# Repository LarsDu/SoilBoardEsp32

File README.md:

# SoilBoardEsp32

A custom PCB for the ESP32-S3-WROOM-1 designed for WiFi enabled and battery powered automated plant watering.

Could also be used to control a dual propeller drone.

Certain parts of the circuit schematic were sourced/adapted from the [LiteWing](https://github.com/Circuit-Digest/LiteWing/tree/main) open source drone project.

Setup with:
 - 2 Screw terminals for 3-4V DC water pumps
 - 2 Capacitative soil moisture sensors
 - Either a DHT-40 or AHT-40 temperature/humidity sensor
 - An optional TFT display
 - 2 optional servo headers
 - An optional ping sensor header for water level detection

This is my first-time PCB design and assembly attempt. This repo may be updated as I make more progress on actual construction.

# Getting started

Board schematics can be opened in KiCad under [`hardware/soilboard/soilboard.kicad_pro`](hardware/soilboard/soilboard.kicad_pro).

Gerber files for each production version can be found under [`hardware/soilboard/production/`](hardware/soilboard/production/)

## Images

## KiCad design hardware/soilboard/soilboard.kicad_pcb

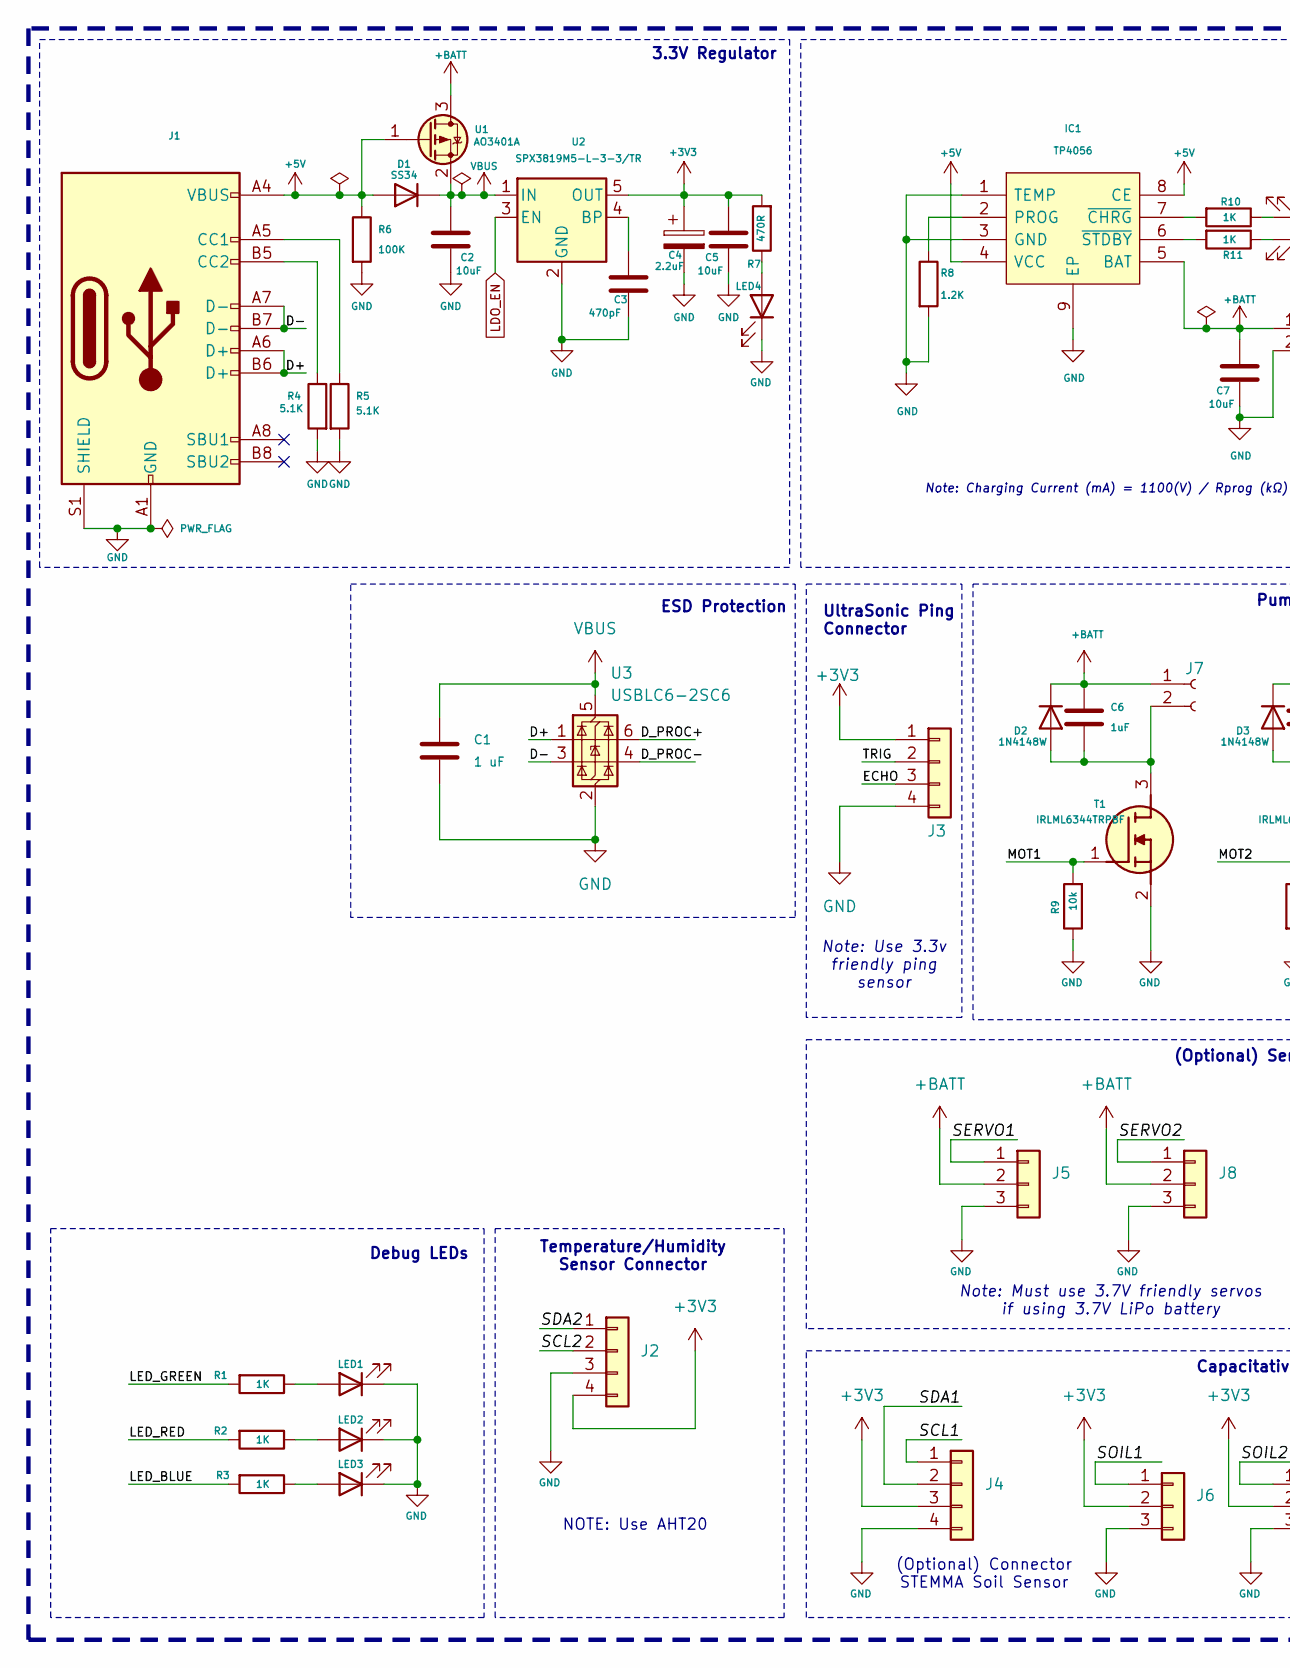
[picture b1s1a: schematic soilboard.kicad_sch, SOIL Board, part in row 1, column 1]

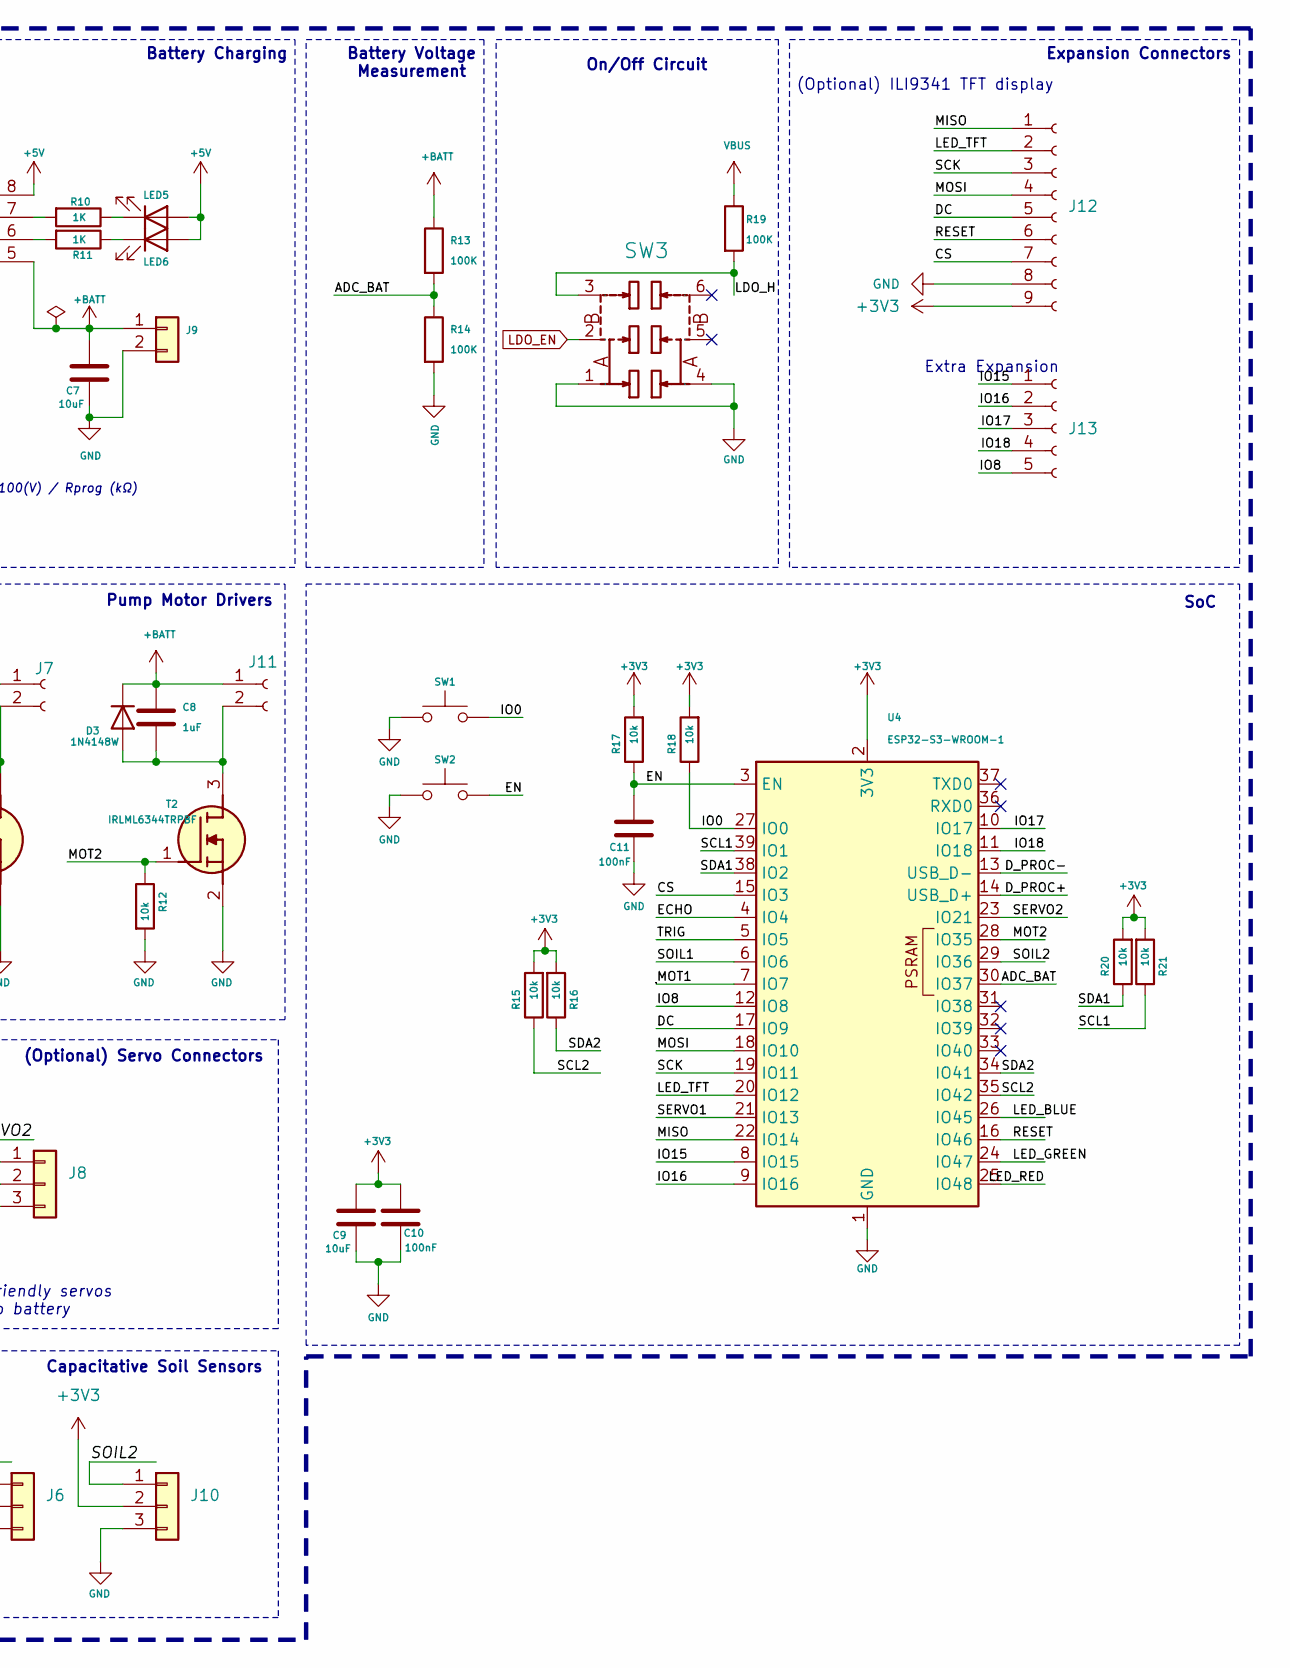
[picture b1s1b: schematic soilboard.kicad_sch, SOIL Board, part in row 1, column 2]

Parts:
C1: 1 uF; C_0603_1608Metric
C2, C5, C7, C9: 10uF; C_0603_1608Metric; MFR.Part # CL10A106KP8NNNC; LCSC Part # C19702
C3: 470pF; C_0603_1608Metric; MFR.Part # 0603B471K500NT; LCSC Part # C1620
C4: 2.2uF; C_0805_2012Metric; MFR.Part # TCC0805X7R225M250FT; LCSC Part # C5448893
C6, C8: 1uF; C_0603_1608Metric; MFR.Part # CL10A105KB8NNNC; LCSC Part # C15849
C10, C11: 100nF; C_0603_1608Metric; MFR.Part # CC0603KRX7R9BB104; LCSC Part # C14663
D1: SS34; D_SMA; MFR.Part # SS34; LCSC Part # C8678
D2, D3: 1N4148W; D_SOD-123; MFR.Part # 1N4148W; LCSC Part # C81598
IC1: TP4056; SOIC127P600X175-9N; MFR.Part # TP4056; LCSC Part # C20199357
J1: USB_C_Receptacle_USB2.0; USB_C_Receptacle_HRO_TYPE-C-31-M-12; MFR.Part # USB-TYPE-C-018; LCSC Part # C2927038
J2: Temp_01x04; PinHeader_1x04_P2.54mm_Vertical
J3: Ping_01x04; PinHeader_1x04_P2.54mm_Vertical
J4: Stemma_01x04; PinHeader_1x04_P2.54mm_Vertical
J5, J6, J8, J10: Conn_01x03; PinHeader_1x03_P2.54mm_Vertical
J7, J11: Conn_01x02_Socket; TerminalBlock_bornier-2_P5.08mm
J9: JST XH 2P 2.50mm SMD Hoz; CONN-TH_2P-P2.50_XH-2AW; MFR.Part # XH-2AW; LCSC Part # C33132
J12: Conn_01x09_Socket; PinSocket_1x09_P2.54mm_Vertical
J13: Extra_01x04_Socket; PinHeader_1x05_P2.54mm_Vertical
LED1: LED_Green; LED_0603_1608Metric; MFR.Part # LTST-C193TGKT-5A; LCSC Part # C12065
LED2, LED4, LED5: LED_Red; LED_0603_1608Metric; MFR.Part # KT-0603R; LCSC Part # C2286
LED3, LED6: LED_Blue; LED_0603_1608Metric; MFR.Part # KT-0603B; LCSC Part # C2288
R1, R2, R3, R10, R11: 1K; R_0603_1608Metric; MFR.Part # 0603WAF1001T5E; LCSC Part # C21190
R4, R5: 5.1K; R_0603_1608Metric; MFR.Part # 0603WAF5101T5E; LCSC Part # C23186
R6, R13, R14, R19: 100K; R_0603_1608Metric; MFR.Part # 0603WAF1003T5E; LCSC Part # C25803
R7: 470R; R_0603_1608Metric; MFR.Part # 0603WAF4700T5E; LCSC Part # C23179
R8: 1.2K; R_0603_1608Metric; MFR.Part # 0603WAF1201T5E; LCSC Part # C22765
R9, R12, R15, R16, R17, R18, R20, R21: 10k; R_0603_1608Metric; MFR.Part # 0603WAF1002T5E; LCSC Part # C25804
SW1, SW2: Tactile Switch 3x4x2; Tactile 3x4x2mm TS-A010; MFR.Part # TS-KG88C-ART25F; LCSC Part # C2874433
SW3: MST22D18G2_125; SW-SMD_MST22D18G2; MFR.Part # MST22D18G2 125; LCSC Part # C2906280
T1, T2: IRLML6344TRPBF; SOT95P237X112-3N; MFR.Part # IRLML6344TRPBF-HXY; LCSC Part # C6285738
U1: AO3401A; SOT-23; MFR.Part # AO3401A; LCSC Part # C15127
U2: SPX3819M5-L-3-3/TR; SOT-23-5; MFR.Part # SPX3819M5-L-3-3/TR; LCSC Part # C9055
U3: USBLC6-2SC6; SOT-23-6
U4: ESP32-S3-WROOM-1; MFR.Part # ESP32-S3-WROOM-1-N8; LCSC Part # C2913198

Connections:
+3V3: C4.1, C5.1, C9.1, C10.1, J2.4, J3.1, J4.3, J6.2, J10.2, J12.9, R7.2, R15.2, R16.2, R17.2, R18.2, R20.2, R21.2, U2.5 (OUT), U4.2 (3V3)
+5V: D1.2 (A), IC1.4 (VCC), IC1.8 (CE), J1.A4 (VBUS), J1.A9 (VBUS), J1.B4 (VBUS), J1.B9 (VBUS), LED5.2 (A), LED6.2 (A), R6.1, U1.1 (G)
+BATT: C6.1, C7.1, C8.1, D2.1 (K), D3.1 (K), IC1.5 (BAT), J5.2, J7.1, J8.2, J9.1, J11.1, R13.1, U1.3 (D)
/ADC_BAT: R13.2, R14.1, U4.30 (IO37)
/CS: J12.7, U4.15 (IO3)
/D+: J1.A6 (D+), J1.B6 (D+), U3.1 (I/O1)
/D-: J1.A7 (D-), J1.B7 (D-), U3.3 (I/O2)
/DC: J12.5, U4.17 (IO9)
/D_PROC+: U3.6 (I/O1), U4.14 (USB_D+)
/D_PROC-: U3.4 (I/O2), U4.13 (USB_D-)
/ECHO: J3.3, U4.4 (IO4)
/EN: C11.1, R17.1, SW2.2, U4.3 (EN)
/IO0: R18.1, SW1.2, U4.27 (IO0)
/IO8: J13.5, U4.12 (IO8)
/IO15: J13.1, U4.8 (IO15)
/IO16: J13.2, U4.9 (IO16)
/IO17: J13.3, U4.10 (IO17)
/IO18: J13.4, U4.11 (IO18)
/LDO_H: R19.2, SW3.3
/LED_BLUE: R3.2, U4.26 (IO45)
/LED_GREEN: R1.2, U4.24 (IO47)
/LED_RED: R2.2, U4.25 (IO48)
/LED_TFT: J12.2, U4.20 (IO12)
/MISO: J12.1, U4.22 (IO14)
/MOSI: J12.4, U4.18 (IO10)
/MOT1: R9.2, T1.1 (G), U4.7 (IO7)
/MOT2: R12.1, T2.1 (G), U4.28 (IO35)
/RESET: J12.6, U4.16 (IO46)
/SCK: J12.3, U4.19 (IO11)
/SCL1: J4.1, R21.1, U4.39 (IO1)
/SCL2: J2.2, R15.1, U4.35 (IO42)
/SDA1: J4.2, R20.1, U4.38 (IO2)
/SDA2: J2.1, R16.1, U4.34 (IO41)
/SERVO1: J5.1, U4.21 (IO13)
/SERVO2: J8.1, U4.23 (IO21)
/SOIL1: J6.1, U4.6 (IO6)
/SOIL2: J10.1, U4.29 (IO36)
/TRIG: J3.2, U4.5 (IO5)
GND: C1.2, C2.2, C3.2, C4.2, C5.2, C7.2, C9.2, C10.2, C11.2, IC1.1 (TEMP), IC1.3 (GND), IC1.9 (EP), J1.A1 (GND), J1.A12 (GND), J1.B1 (GND), J1.B12 (GND), J1.S1 (SHIELD), J2.3, J3.4, J4.4, J5.3, J6.3, J8.3, J9.2, J10.3, J12.8, LED1.1 (K), LED2.1 (K), LED3.1 (K), LED4.1 (K), R4.2, R5.2, R6.2, R8.2, R9.1, R12.2, R14.2, SW1.1, SW2.1, SW3.1, SW3.4, T1.2 (S), T2.2 (S), U2.2 (GND), U3.2 (GND), U4.1 (GND), U4.40 (GND), U4.41 (GND)
LDO_EN: SW3.2, U2.3 (EN)
unnamed: C6.2, D2.2 (A), J7.2, T1.3 (D)
unnamed: C8.2, D3.2 (A), J11.2, T2.3 (D)
unnamed: IC1.2 (PROG), R8.1
unnamed: IC1.7 (~CHRG), R10.2
unnamed: IC1.6 (~STDBY), R11.2
unnamed: J1.A5 (CC1), R5.1
unnamed: J1.B5 (CC2), R4.1
unnamed: LED1.2 (A), R1.1
unnamed: LED2.2 (A), R2.1
unnamed: LED3.2 (A), R3.1
unnamed: LED4.2 (A), R7.1
unnamed: LED5.1 (K), R10.1
unnamed: LED6.1 (K), R11.1
unnamed: C3.1, U2.4 (BP)
VBUS: C1.1, C2.1, D1.1 (K), R19.1, U1.2 (S), U2.1 (IN), U3.5 (VBUS)

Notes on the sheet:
Capacitative Soil Sensors
Expansion Connectors
3.3V Regulator
SoC
Temperature/Humidity Sensor Connector
Battery Charging
(Optional) Servo Connectors
Battery Voltage Measurement
Debug LEDs
(Optional) Connector STEMMA Soil Sensor
Note: Must use 3.7V friendly servos if using 3.7V LiPo battery
UltraSonic Ping Connector
Extra Expansion
Note: Charging Current (mA) = 1100(V) / Rprog (kΩ)
Note: Use 3.3v friendly ping sensor
On/Off Circuit
(Optional) ILI9341 TFT display
NOTE: Use AHT20
Pump Motor Drivers
ESD Protection

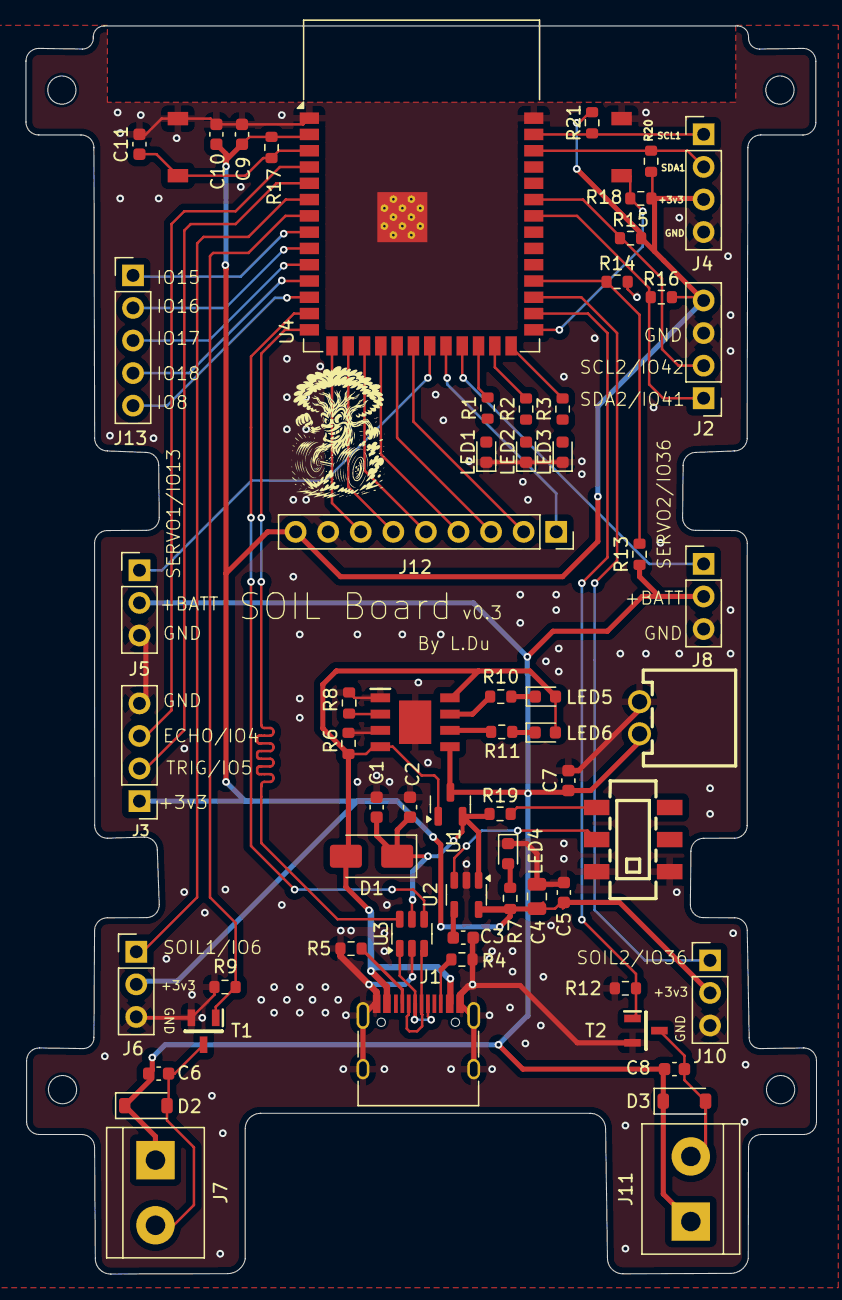
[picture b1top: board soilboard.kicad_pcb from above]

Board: 2 copper layers, 61.7 x 97.3 mm, 64 parts (0 on the bottom side), 55 nets.

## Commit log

2025-07-21 First commit.
2025-07-21 Renamings.
2025-07-21 Attribution to Litewing project.
2025-07-26 SOILBoard v0.3 send off for manufacturing.
2025-07-26 Updated README.
2025-07-26 Posible update.
